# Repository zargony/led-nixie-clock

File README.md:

# LED Nixie Clock

An attempt to build my own LED Nixie Clock

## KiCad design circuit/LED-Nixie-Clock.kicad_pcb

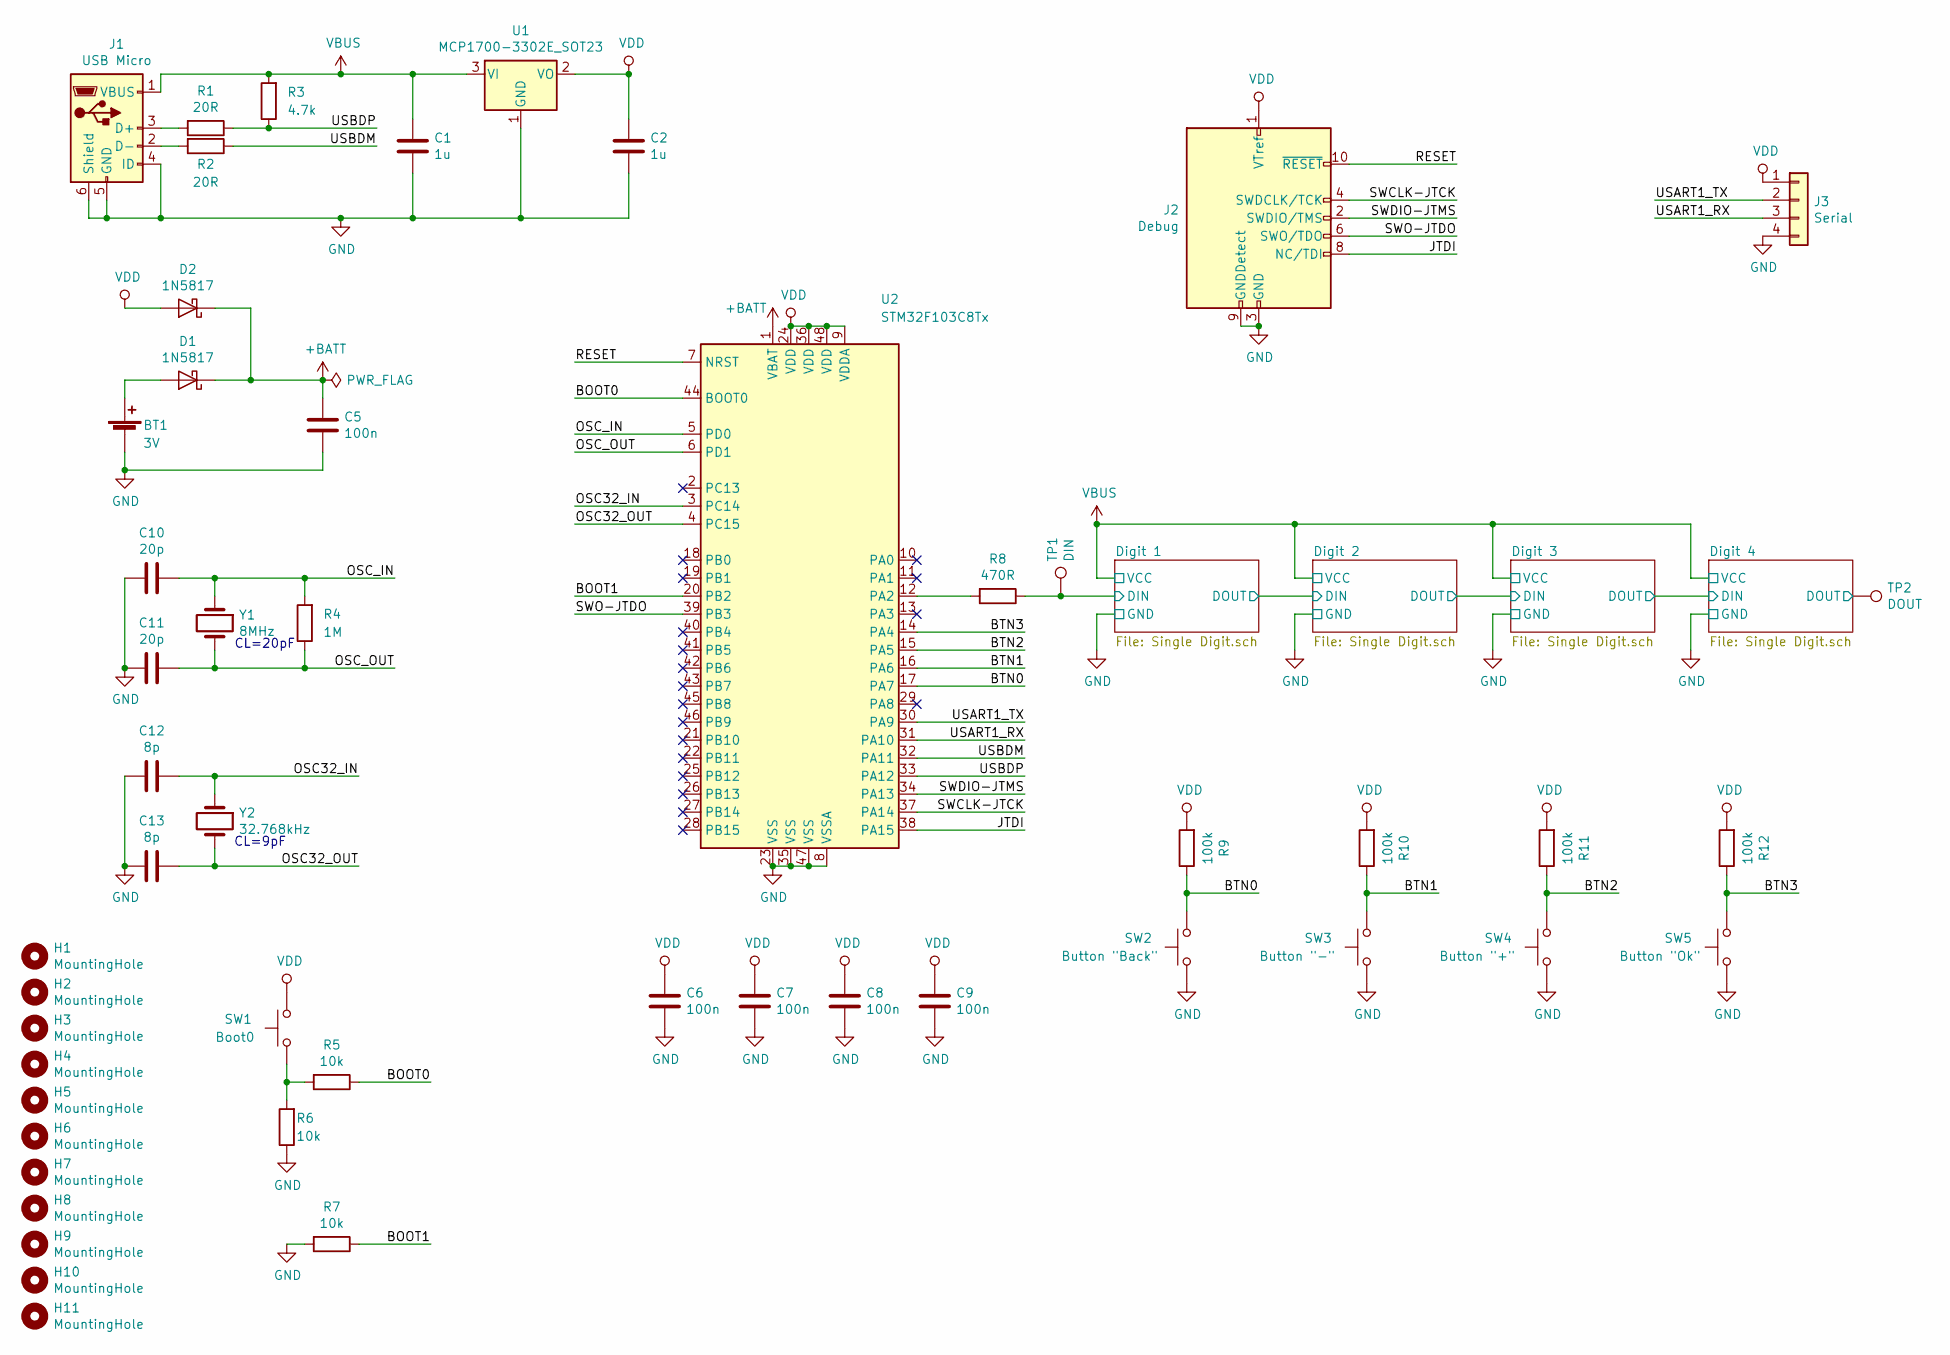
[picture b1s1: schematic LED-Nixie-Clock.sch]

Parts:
BT1: 3V; BatteryHolder_Keystone_1058_1x2032
C1, C2: 1u; C_0805_2012Metric_Pad1.15x1.40mm_HandSolder
C5, C6, C7, C8, C9: 100n; C_0805_2012Metric_Pad1.15x1.40mm_HandSolder
C10, C11: 20p; C_0805_2012Metric_Pad1.15x1.40mm_HandSolder
C12, C13: 8p; C_0805_2012Metric_Pad1.15x1.40mm_HandSolder
D1, D2: 1N5817; D_0805_2012Metric_Pad1.15x1.40mm_HandSolder
H1, H2, H3, H4, H5, H6, H7, H8, H9, H10, H11: MountingHole; MountingHole_3.2mm_M3_ISO7380
J1: USB Micro; USB_Micro-B_Wuerth_629105150521
J2: Debug; PinHeader_2x05_P1.27mm_Vertical_SMD
J3: Serial; PinHeader_1x04_P2.54mm_Vertical
R1, R2: 20R; R_0805_2012Metric_Pad1.15x1.40mm_HandSolder
R3: 4.7k; R_0805_2012Metric_Pad1.15x1.40mm_HandSolder
R4: 1M; R_0805_2012Metric_Pad1.15x1.40mm_HandSolder
R5, R6, R7: 10k; R_0805_2012Metric_Pad1.15x1.40mm_HandSolder
R8: 470R; R_0805_2012Metric_Pad1.15x1.40mm_HandSolder
R9, R10, R11, R12: 100k; R_0805_2012Metric_Pad1.15x1.40mm_HandSolder
SW1: Boot0; SW_SPST_CK_RS282G05A3
SW2: Button \"Back\"; SW_Push_1P1T_NO_6x6mm_H9.5mm
SW3: Button \"-\"; SW_Push_1P1T_NO_6x6mm_H9.5mm
SW4: Button \"+\"; SW_Push_1P1T_NO_6x6mm_H9.5mm
SW5: Button \"Ok\"; SW_Push_1P1T_NO_6x6mm_H9.5mm
TP1: DIN; TestPoint_Pad_2.5x2.5mm
TP2: DOUT; TestPoint_Pad_2.5x2.5mm
U1: MCP1700-3302E_SOT23; SOT-23_Handsoldering
U2: STM32F103C8Tx; LQFP-48_7x7mm_P0.5mm
Y1: 8MHz; Crystal_SMD_5032-2Pin_5.0x3.2mm
Y2: 32.768kHz; Crystal_SMD_3215-2Pin_3.2x1.5mm

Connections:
+BATT: C5.1, D1.1 (K), D2.1 (K), U2.1 (VBAT)
/BOOT0: R5.1, U2.44 (BOOT0)
/BOOT1: R7.1, U2.20 (PB2)
/BTN0: R9.1, SW2.2, U2.17 (PA7)
/BTN1: R10.1, SW3.2, U2.16 (PA6)
/BTN2: R11.1, SW4.2, U2.15 (PA5)
/BTN3: R12.1, SW5.2, U2.14 (PA4)
/Digit 1/DIN: R8.1, TP1.1; also elsewhere on the board
/Digit 4/DOUT: TP2.1; also elsewhere on the board
/JTDI: J2.8 (NC/TDI), U2.38 (PA15)
/OSC32_IN: C12.1, U2.3 (PC14), Y2.1
/OSC32_OUT: C13.1, U2.4 (PC15), Y2.2
/OSC_IN: C10.1, R4.2, U2.5 (PD0), Y1.1
/OSC_OUT: C11.1, R4.1, U2.6 (PD1), Y1.2
/RESET: J2.10 (~RESET~), U2.7 (NRST)
/SWCLK-JTCK: J2.4 (SWDCLK/TCK), U2.37 (PA14)
/SWDIO-JTMS: J2.2 (SWDIO/TMS), U2.34 (PA13)
/SWO-JTDO: J2.6 (SWO/TDO), U2.39 (PB3)
/USART1_RX: J3.3, U2.31 (PA10)
/USART1_TX: J3.2, U2.30 (PA9)
/USBDM: R2.1, U2.32 (PA11)
/USBDP: R1.1, R3.1, U2.33 (PA12)
GND: BT1.2 (-), C1.2, C2.2, C5.2, C6.2, C7.2, C8.2, C9.2, C10.2, C11.2, C12.2, C13.2, J1.4 (ID), J1.5 (GND), J1.6 (Shield), J2.3 (GND), J2.5 (GND), J2.9 (GNDDetect), J3.4, R6.1, R7.2, SW2.1, SW3.1, SW4.1, SW5.1, U1.1 (GND), U2.8 (VSSA), U2.23 (VSS), U2.35 (VSS), U2.47 (VSS); also elsewhere on the board
unnamed: BT1.1 (+), D1.2 (A)
unnamed: J1.2 (D-), R2.2
unnamed: J1.3 (D+), R1.2
unnamed: R5.2, R6.2, SW1.1
unnamed: R8.2, U2.12 (PA2)
VBUS: C1.1, J1.1 (VBUS), R3.2, U1.3 (VI); also elsewhere on the board
VDD: C2.1, C6.1, C7.1, C8.1, C9.1, D2.2 (A), J2.1 (VTref), J3.1, R9.2, R10.2, R11.2, R12.2, SW1.2, U1.2 (VO), U2.9 (VDDA), U2.24 (VDD), U2.36 (VDD), U2.48 (VDD)

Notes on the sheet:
CL=20pF
CL=9pF

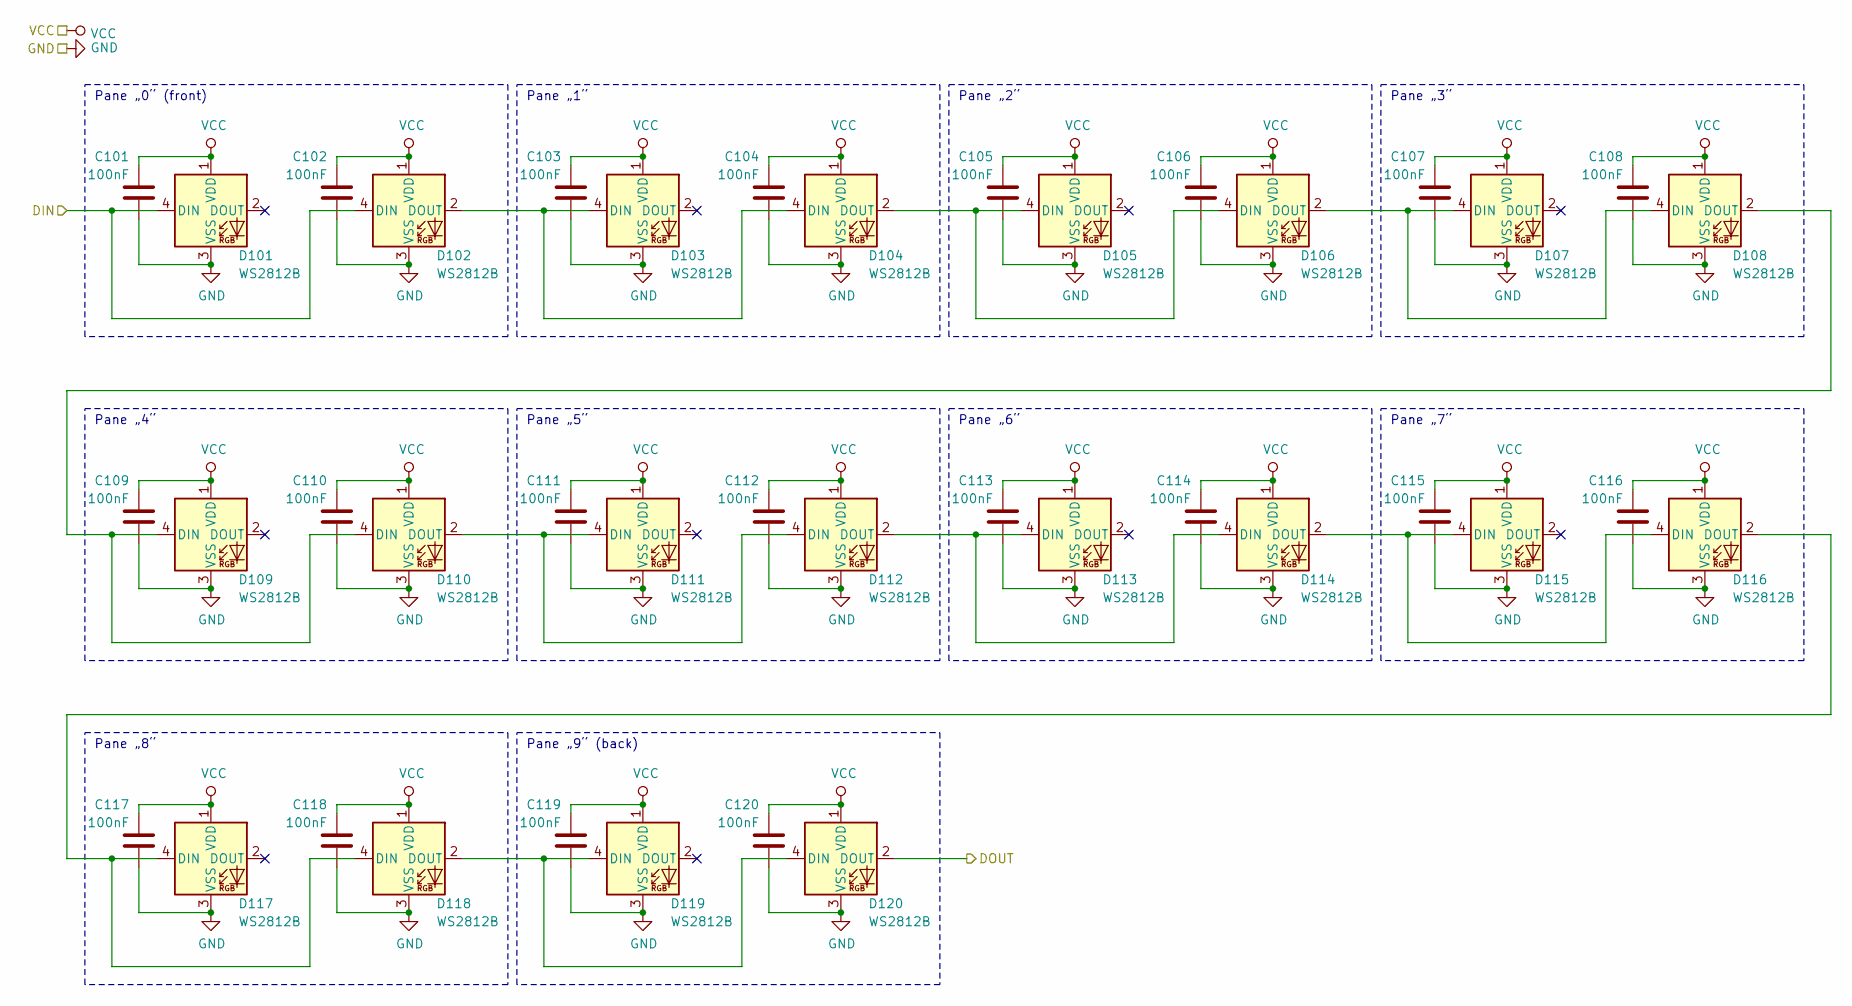
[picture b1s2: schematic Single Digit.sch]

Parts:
C101, C102, C103, C104, C105, C106, C107, C108, C109, C110, C111, C112, C113, C114, C115, C116, C117, C118, C119, C120: 100nF; C_0805_2012Metric_Pad1.15x1.40mm_HandSolder
D101, D102, D103, D104, D105, D106, D107, D108, D109, D110, D111, D112, D113, D114, D115, D116, D117, D118, D119, D120: WS2812B; LED_WS2812B_PLCC4_5.0x5.0mm_P3.2mm

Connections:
/Digit 1/DIN: D101.4 (DIN), D102.4 (DIN); also elsewhere on the board
/Digit 2/DIN: D120.2 (DOUT); also elsewhere on the board
GND: C101.2, C102.2, C103.2, C104.2, C105.2, C106.2, C107.2, C108.2, C109.2, C110.2, C111.2, C112.2, C113.2, C114.2, C115.2, C116.2, C117.2, C118.2, C119.2, C120.2, D101.3 (VSS), D102.3 (VSS), D103.3 (VSS), D104.3 (VSS), D105.3 (VSS), D106.3 (VSS), D107.3 (VSS), D108.3 (VSS), D109.3 (VSS), D110.3 (VSS), D111.3 (VSS), D112.3 (VSS), D113.3 (VSS), D114.3 (VSS), D115.3 (VSS), D116.3 (VSS), D117.3 (VSS), D118.3 (VSS), D119.3 (VSS), D120.3 (VSS); also elsewhere on the board
unnamed: D102.2 (DOUT), D103.4 (DIN), D104.4 (DIN)
unnamed: D104.2 (DOUT), D105.4 (DIN), D106.4 (DIN)
unnamed: D106.2 (DOUT), D107.4 (DIN), D108.4 (DIN)
unnamed: D108.2 (DOUT), D109.4 (DIN), D110.4 (DIN)
unnamed: D110.2 (DOUT), D111.4 (DIN), D112.4 (DIN)
unnamed: D112.2 (DOUT), D113.4 (DIN), D114.4 (DIN)
unnamed: D114.2 (DOUT), D115.4 (DIN), D116.4 (DIN)
unnamed: D116.2 (DOUT), D117.4 (DIN), D118.4 (DIN)
unnamed: D118.2 (DOUT), D119.4 (DIN), D120.4 (DIN)
VBUS: C101.1, C102.1, C103.1, C104.1, C105.1, C106.1, C107.1, C108.1, C109.1, C110.1, C111.1, C112.1, C113.1, C114.1, C115.1, C116.1, C117.1, C118.1, C119.1, C120.1, D101.1 (VDD), D102.1 (VDD), D103.1 (VDD), D104.1 (VDD), D105.1 (VDD), D106.1 (VDD), D107.1 (VDD), D108.1 (VDD), D109.1 (VDD), D110.1 (VDD), D111.1 (VDD), D112.1 (VDD), D113.1 (VDD), D114.1 (VDD), D115.1 (VDD), D116.1 (VDD), D117.1 (VDD), D118.1 (VDD), D119.1 (VDD), D120.1 (VDD); also elsewhere on the board

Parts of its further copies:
C201, C202, C203, C204, C205, C206, C207, C208, C209, C210, C211, C212, C213, C214, C215, C216, C217, C218, C219, C220, C301, C302, C303, C304, C305, C306, C307, C308, C309, C310, C311, C312, C313, C314, C315, C316, C317, C318, C319, C320, C401, C402, C403, C404, C405, C406, C407, C408, C409, C410, C411, C412, C413, C414, C415, C416, C417, C418, C419, C420: 100nF; C_0805_2012Metric_Pad1.15x1.40mm_HandSolder
D201, D202, D203, D204, D205, D206, D207, D208, D209, D210, D211, D212, D213, D214, D215, D216, D217, D218, D219, D220, D301, D302, D303, D304, D305, D306, D307, D308, D309, D310, D311, D312, D313, D314, D315, D316, D317, D318, D319, D320, D401, D402, D403, D404, D405, D406, D407, D408, D409, D410, D411, D412, D413, D414, D415, D416, D417, D418, D419, D420: WS2812B; LED_WS2812B_PLCC4_5.0x5.0mm_P3.2mm

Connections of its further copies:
/Digit 2/DIN: D201.4 (DIN), D202.4 (DIN); also elsewhere on the board
/Digit 3/DIN: D220.2 (DOUT), D301.4 (DIN), D302.4 (DIN)
/Digit 4/DIN: D320.2 (DOUT), D401.4 (DIN), D402.4 (DIN)
/Digit 4/DOUT: D420.2 (DOUT); also elsewhere on the board
GND: C201.2, C202.2, C203.2, C204.2, C205.2, C206.2, C207.2, C208.2, C209.2, C210.2, C211.2, C212.2, C213.2, C214.2, C215.2, C216.2, C217.2, C218.2, C219.2, C220.2, C301.2, C302.2, C303.2, C304.2, C305.2, C306.2, C307.2, C308.2, C309.2, C310.2, C311.2, C312.2, C313.2, C314.2, C315.2, C316.2, C317.2, C318.2, C319.2, C320.2, C401.2, C402.2, C403.2, C404.2, C405.2, C406.2, C407.2, C408.2, C409.2, C410.2, C411.2, C412.2, C413.2, C414.2, C415.2, C416.2, C417.2, C418.2, C419.2, C420.2, D201.3 (VSS), D202.3 (VSS), D203.3 (VSS), D204.3 (VSS), D205.3 (VSS), D206.3 (VSS), D207.3 (VSS), D208.3 (VSS), D209.3 (VSS), D210.3 (VSS), D211.3 (VSS), D212.3 (VSS), D213.3 (VSS), D214.3 (VSS), D215.3 (VSS), D216.3 (VSS), D217.3 (VSS), D218.3 (VSS), D219.3 (VSS), D220.3 (VSS), D301.3 (VSS), D302.3 (VSS), D303.3 (VSS), D304.3 (VSS), D305.3 (VSS), D306.3 (VSS), D307.3 (VSS), D308.3 (VSS), D309.3 (VSS), D310.3 (VSS), D311.3 (VSS), D312.3 (VSS), D313.3 (VSS), D314.3 (VSS), D315.3 (VSS), D316.3 (VSS), D317.3 (VSS), D318.3 (VSS), D319.3 (VSS), D320.3 (VSS), D401.3 (VSS), D402.3 (VSS), D403.3 (VSS), D404.3 (VSS), D405.3 (VSS), D406.3 (VSS), D407.3 (VSS), D408.3 (VSS), D409.3 (VSS), D410.3 (VSS), D411.3 (VSS), D412.3 (VSS), D413.3 (VSS), D414.3 (VSS), D415.3 (VSS), D416.3 (VSS), D417.3 (VSS), D418.3 (VSS), D419.3 (VSS), D420.3 (VSS); also elsewhere on the board
unnamed: D202.2 (DOUT), D203.4 (DIN), D204.4 (DIN)
unnamed: D204.2 (DOUT), D205.4 (DIN), D206.4 (DIN)
unnamed: D206.2 (DOUT), D207.4 (DIN), D208.4 (DIN)
unnamed: D208.2 (DOUT), D209.4 (DIN), D210.4 (DIN)
unnamed: D210.2 (DOUT), D211.4 (DIN), D212.4 (DIN)
unnamed: D212.2 (DOUT), D213.4 (DIN), D214.4 (DIN)
unnamed: D214.2 (DOUT), D215.4 (DIN), D216.4 (DIN)
unnamed: D216.2 (DOUT), D217.4 (DIN), D218.4 (DIN)
unnamed: D218.2 (DOUT), D219.4 (DIN), D220.4 (DIN)
unnamed: D302.2 (DOUT), D303.4 (DIN), D304.4 (DIN)
unnamed: D304.2 (DOUT), D305.4 (DIN), D306.4 (DIN)
unnamed: D306.2 (DOUT), D307.4 (DIN), D308.4 (DIN)
unnamed: D308.2 (DOUT), D309.4 (DIN), D310.4 (DIN)
unnamed: D310.2 (DOUT), D311.4 (DIN), D312.4 (DIN)
unnamed: D312.2 (DOUT), D313.4 (DIN), D314.4 (DIN)
unnamed: D314.2 (DOUT), D315.4 (DIN), D316.4 (DIN)
unnamed: D316.2 (DOUT), D317.4 (DIN), D318.4 (DIN)
unnamed: D318.2 (DOUT), D319.4 (DIN), D320.4 (DIN)
unnamed: D402.2 (DOUT), D403.4 (DIN), D404.4 (DIN)
unnamed: D404.2 (DOUT), D405.4 (DIN), D406.4 (DIN)
unnamed: D406.2 (DOUT), D407.4 (DIN), D408.4 (DIN)
unnamed: D408.2 (DOUT), D409.4 (DIN), D410.4 (DIN)
unnamed: D410.2 (DOUT), D411.4 (DIN), D412.4 (DIN)
unnamed: D412.2 (DOUT), D413.4 (DIN), D414.4 (DIN)
unnamed: D414.2 (DOUT), D415.4 (DIN), D416.4 (DIN)
unnamed: D416.2 (DOUT), D417.4 (DIN), D418.4 (DIN)
unnamed: D418.2 (DOUT), D419.4 (DIN), D420.4 (DIN)
VBUS: C201.1, C202.1, C203.1, C204.1, C205.1, C206.1, C207.1, C208.1, C209.1, C210.1, C211.1, C212.1, C213.1, C214.1, C215.1, C216.1, C217.1, C218.1, C219.1, C220.1, C301.1, C302.1, C303.1, C304.1, C305.1, C306.1, C307.1, C308.1, C309.1, C310.1, C311.1, C312.1, C313.1, C314.1, C315.1, C316.1, C317.1, C318.1, C319.1, C320.1, C401.1, C402.1, C403.1, C404.1, C405.1, C406.1, C407.1, C408.1, C409.1, C410.1, C411.1, C412.1, C413.1, C414.1, C415.1, C416.1, C417.1, C418.1, C419.1, C420.1, D201.1 (VDD), D202.1 (VDD), D203.1 (VDD), D204.1 (VDD), D205.1 (VDD), D206.1 (VDD), D207.1 (VDD), D208.1 (VDD), D209.1 (VDD), D210.1 (VDD), D211.1 (VDD), D212.1 (VDD), D213.1 (VDD), D214.1 (VDD), D215.1 (VDD), D216.1 (VDD), D217.1 (VDD), D218.1 (VDD), D219.1 (VDD), D220.1 (VDD), D301.1 (VDD), D302.1 (VDD), D303.1 (VDD), D304.1 (VDD), D305.1 (VDD), D306.1 (VDD), D307.1 (VDD), D308.1 (VDD), D309.1 (VDD), D310.1 (VDD), D311.1 (VDD), D312.1 (VDD), D313.1 (VDD), D314.1 (VDD), D315.1 (VDD), D316.1 (VDD), D317.1 (VDD), D318.1 (VDD), D319.1 (VDD), D320.1 (VDD), D401.1 (VDD), D402.1 (VDD), D403.1 (VDD), D404.1 (VDD), D405.1 (VDD), D406.1 (VDD), D407.1 (VDD), D408.1 (VDD), D409.1 (VDD), D410.1 (VDD), D411.1 (VDD), D412.1 (VDD), D413.1 (VDD), D414.1 (VDD), D415.1 (VDD), D416.1 (VDD), D417.1 (VDD), D418.1 (VDD), D419.1 (VDD), D420.1 (VDD); also elsewhere on the board

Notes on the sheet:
Pane „0“ (front)
Pane „1“
Pane „2“
Pane „3“
Pane „4“
Pane „5“
Pane „6“
Pane „7“
Pane „8“
Pane „9“ (back)

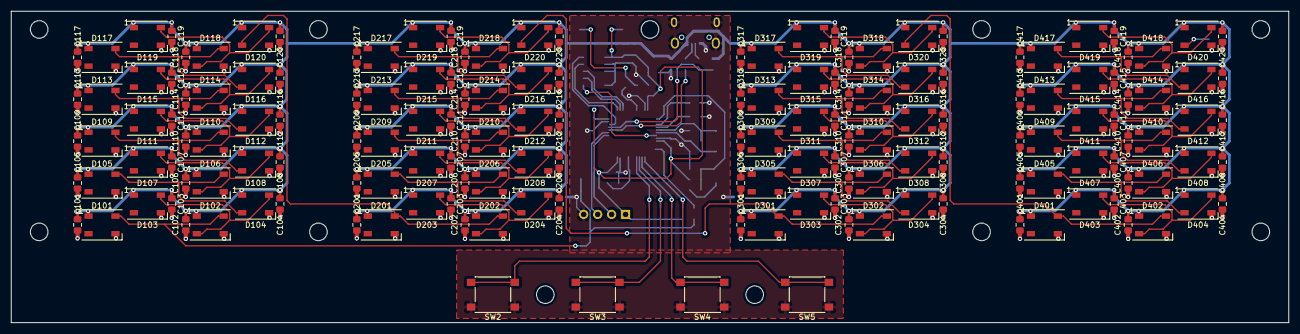
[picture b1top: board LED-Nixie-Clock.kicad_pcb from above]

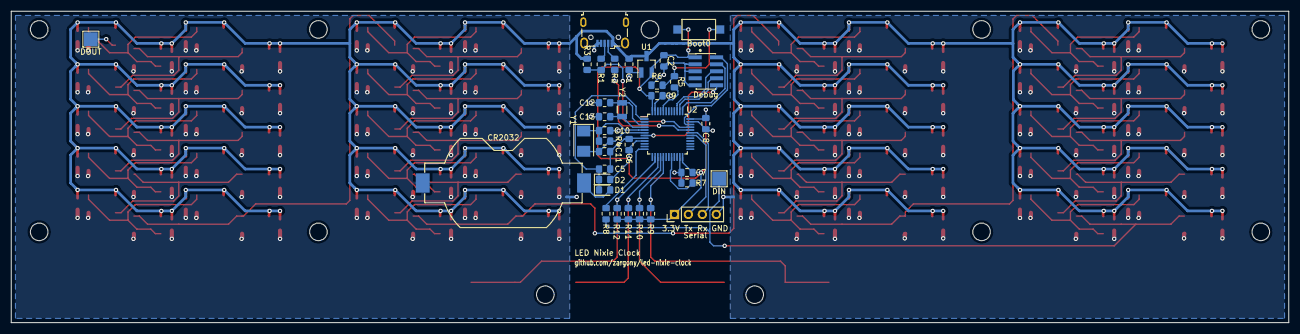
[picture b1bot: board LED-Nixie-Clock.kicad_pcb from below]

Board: 2 copper layers, 232.4 x 56.6 mm, 211 parts (36 on the bottom side), 69 nets.

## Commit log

2018-09-21 Let's start
2018-10-07 First design of a digit pane
2018-10-07 Stack digit panes
2019-01-10 Reorganize and switch to 3mm digit panes (v4)
2019-01-10 Rename and add simple base block (v5)
2019-01-11 Arrange base and digit panes (v8)
2019-01-12 Add basic circuit schematics
2019-01-15 Improve schematics, add crystals, USB connector, power regulator, backup battery
2019-01-16 Add a test point at DOUT of the last LED
2019-01-16 Use MCP1700 linear regulator instead of LM1117
2019-01-16 Add mounting holes
2019-01-17 Add proper boot jumper and fix some footprints
2019-01-17 Fix oscillator capacitances
2019-01-18 Initial pcb with basic LED and controller layout (still incomplete)
2019-01-18 Add SWD/JTAG debug port
2019-01-18 Fix DRC problems
2019-01-19 Add 3d model for WS2812B LEDs
2019-01-19 Fix GND zone filling
2019-01-20 Improve spacing around debug connector
2019-01-20 Improve silk layer labels
2019-01-22 Add serial port and replace reset with a boot select pushbutton
2019-01-22 Reroute PCB traces for more compact layout and 5032 crystal
2019-01-22 Move LED data bus to PA2 (which is on the same pin as USART2 Tx)
2019-01-22 Fix USBDP pull up resistor
2019-01-22 Redesign of digit mounting (v11)
2019-02-09 Adjust digit screw gutters (v12)
2019-02-09 Add PCB (v13)
2019-02-21 Move 3d model to subdirectory
2019-10-22 Adjust credits text on PCB
2019-10-22 Add test points for DIN and DOUT, improve front side routing
2019-11-03 Add input buttons
2019-11-03 Enlarge PCB and add more mounting holes
